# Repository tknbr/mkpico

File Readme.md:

# MKPico, a Pi pico USB Keyboard framework

Welcome to **MKPico**, a framework designed for creating custom keyboard firmware using the Raspberry Pi Pico microcontroller. MKPico is built using **FreeRTOS**, **Pico SDK** and **tinyUSB**.

<center>Selenium s (34 keys split mechanical keyboard)</center>

## Overview

This repository is the home of MKPico, and it includes everything you need to get started with developing your own keyboard firmware. MKPico abstracts the complexities of USB communication and real-time task management, providing an easy-to-use framework that is both powerful and efficient.

The first project built using MKPico is Selenium S, a custom 34-key split keyboard that demonstrates the capabilities of the framework. Selenium S serves as a reference implementation and a starting point for your own projects.

The main goals of the project are:

- **Cross-Platform Compatibility**: MKPico ensures that your keyboards work seamlessly across multiple operating systems, including Linux and Windows.
- **Support for Boot and Normal Modes**: The framework fully supports USB boot mode, making your keyboard operational even during system boot (BIOS/UEFI) and in the normal operating system environment.
Real-Time Operating System: Powered by FreeRTOS, MKPico offers real-time task management, allowing for precise control over keyboard functions and responsiveness.
- **USB Protocol Management**: Built on TinyUSB, MKPico handles USB communication reliably, ensuring your keyboard is fully compliant with USB standards.
- **Modular Design**: MKPico’s modular architecture allows you to extend or customize the framework to suit specific needs, whether it’s adding new HID features or integrating with other hardware components.
- **Easy porting to new keyboard designs**: The repository should allow to create new keyboard designs easily by defining a new layout and some key characteristics.

## Project Structure

The MKPico project is organized into several key directories, each serving a specific purpose in the development and configuration of custom keyboards. Below is an overview of the project structure:

- **`config/`**:
  - This folder contains configuration files for specific keyboards. Each keyboard has its own configuration file, which defines settings such as the key layout, pin mappings, and any special features or behaviors unique to that keyboard. By modifying these files, you can easily adapt MKPico to support different keyboard designs.

- **`include/`**:
  - The `include` directory houses the internal API headers that define the interfaces and data structures used throughout the MKPico framework. These headers are essential for maintaining a clear and consistent API across different modules of the project, making it easier to develop and extend functionality.

- **`src/`**:
  - This folder contains the core logic of the MKPico framework. It includes the following components:
    - **Internal I2C Communication**: Manages communication between the split halves of the keyboard, ensuring synchronized key presses and other functions across the two parts.
    - **USB Interface**: Handles the USB communication with the host computer, including enumeration, report generation, and processing of USB HID events.
    - **Logic of Layers and Key Map**: Implements the functionality for keyboard layers and key mapping, allowing users to define multiple layouts and switch between them dynamically.
    - **Keystrokes Handling**: Processes key presses and releases, manages debouncing, and ensures accurate and responsive input detection.

## Getting started

This section guides you through setting up the environment to work with FreeRTOS and the Raspberry Pi Pico SDK.

### 1. Clone FreeRTOS Repository

First, clone the FreeRTOS kernel repository:

```bash
git clone https://github.com/FreeRTOS/FreeRTOS-Kernel.git
cd FreeRTOS-Kernel
```

And move to the smp branch that supports multiple core:

```bash
git checkout -t remotes/origin/smp
git submodule update --init
```

### 2. Clone Pico SDK Repository

Second, clone the Pico SDK repository:

```bash
git clone https://github.com/raspberrypi/pico-sdk.git
cd pico-sdk
git submodule update --init
```

### 3. Set environment variables 

Set environment variables to point to the FreeRTOS and Pico SDK directories:

```bash
export FREERTOS_KERNEL_PATH=/path/to/FreeRTOS-Kernel
export PICO_SDK_PATH=/path/to/pico-sdk
```

### 4. Initialize project code

Now, clone your project repository and initialize it.

```bash
cd /path/to/your/workspace
git clone https://github.com/tknbr/mkpico.git
cd mkpico
git submodule update --init
```

### 5. Set up CMake and Build the Project

You can now set up CMake and build the project:

```bash
mkdir build
cd build
cmake ..
make
```

## Acknowledgements

The development of MKPico and the Selenium S keyboard was greatly influenced and supported by the vibrant communities dedicated to mechanical keyboards and custom firmware development. We would like to extend our gratitude to the following communities and content creators for their invaluable resources, tutorials, and inspiration:

- **Mechanical Keyboard Enthusiasts on GitHub**: The numerous open-source keyboard projects and libraries available on GitHub have been instrumental in shaping the direction of MKPico. Special thanks to repositories like [QMK Firmware](https://github.com/qmk/qmk_firmware), which provided insight into advanced keyboard features and firmware structure.
  
- **YouTube Content Creators**: Channels such as [Joe Scotto](https://www.youtube.com/@joe_scotto) and [Ben Vallack](https://www.youtube.com/c/BenVallack) have offered detailed build guides, reviews, and deep dives into keyboard design that have been incredibly helpful during the development process.

- **Online Keyboard Communities**: Platforms like [r/MechanicalKeyboards](https://www.reddit.com/r/MechanicalKeyboards/) on Reddit, and forums like [Geekhack](https://geekhack.org/), have provided a wealth of information and community support that was crucial in overcoming challenges during the project.

This project would not have been possible without the contributions of these communities, and we encourage anyone interested in custom keyboard development to explore these resources and get involved.

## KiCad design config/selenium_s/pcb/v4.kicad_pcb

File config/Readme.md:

## Configuration Folder Overview

The `config` folder is dedicated to holding all the configuration settings for the different parts of the project. This modular configuration structure allows for easy management and customization of various components of the firmware.

### 1. FreeRTOSConfig.h

**Purpose:**
- `FreeRTOSConfig.h` contains the configuration settings for the FreeRTOS kernel.
- It defines various parameters like task priorities, stack sizes, tick rates, and other kernel-level settings required by FreeRTOS to operate within the environment.

### 2. Compile.h

**Purpose:**
- `compile.h` contains two important defines: `PERIPHERAL` and `CONTROLLER`.
- These defines determine whether the compiled firmware image will be for the peripheral or the controller part of the keyboard.
- **Future Enhancement:** The goal is to eventually move this configuration to the Makefile so that users won't need to modify this file directly.

### 3. Task_Internal.h

**Purpose:**
- `task_internal.h` holds configuration details related to tasks within the firmware.
- This includes default sleep times, sizes of communication queues, default task priorities, and other task-specific settings that influence the behavior and performance of the system.

### 4. Tusb_Config.h

**Purpose:**
- `tusb_config.h` provides the basic configuration settings for the TinyUSB library.
- It includes settings related to USB device functionality, such as endpoint sizes, buffer sizes, and other parameters that TinyUSB requires to manage USB communication.

### 5. Keyboard-Specific Configurations

**Purpose:**
- The `config` folder also contains a subfolder for each keyboard supported by the firmware. Currently, there is one folder called `selenium_s`.
- Each keyboard-specific folder contains the following files:
  - **gpios.h:** Defines the GPIOs associated with each column and row of the keyboard matrix. This file maps the physical layout of the keyboard to the microcontroller's GPIO pins.
  - **keymap.h:** Provides the layout of the rows and columns, linking the physical keyboard matrix to the logical keymap.
  - **keymap.c:** Contains the definition of the keyboard's layout and the specific location of each key. This file is where the actual key mappings (e.g., which key corresponds to which row/column) are defined.
  - **pcb:** this folder contains the schematic and pcb files for the keyboard.

  <center>Selenium s (34 keys split mechanical keyboard) pcb</center>

### Summary

The `config` folder is the backbone of the project's configuration management, encapsulating all necessary settings to customize the FreeRTOS kernel, task behaviors, USB communication, and keyboard layouts. By modularizing these settings into distinct files and folders, the project ensures that configurations are easy to manage, modify, and extend, making the firmware highly adaptable to different hardware configurations and future enhancements.

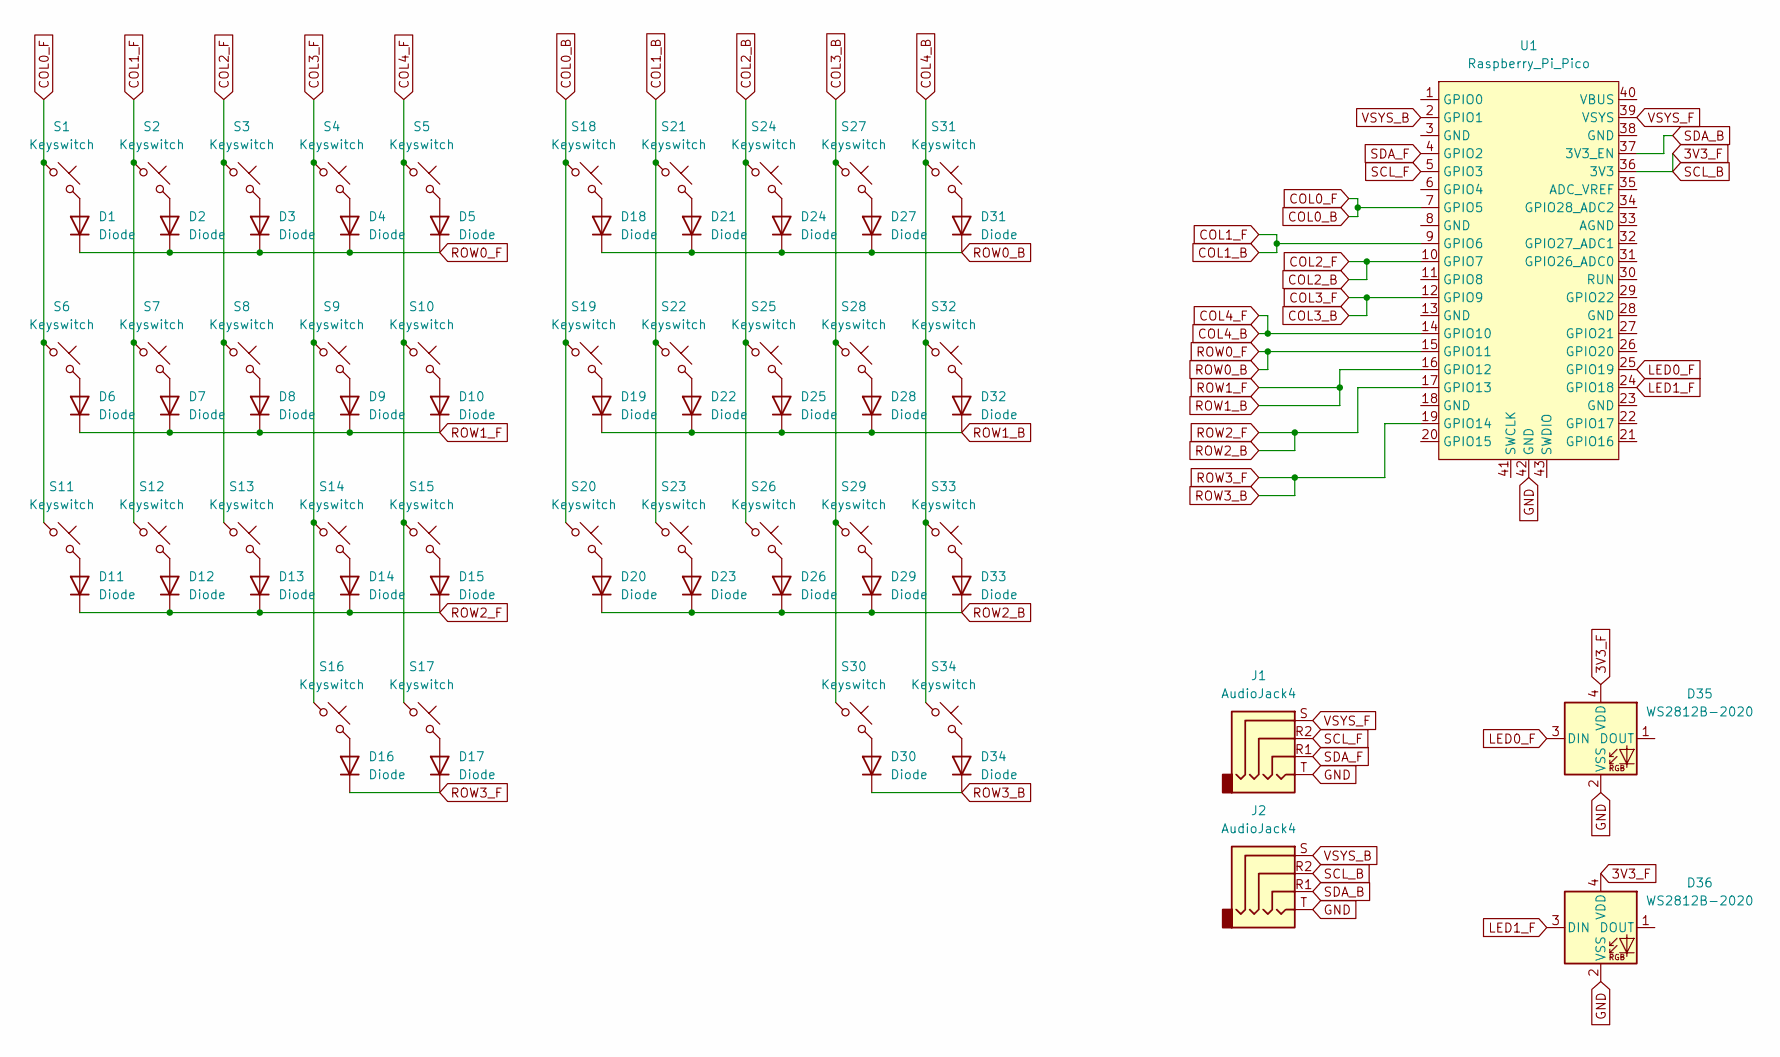
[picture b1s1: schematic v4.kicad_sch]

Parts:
D1, D2, D3, D4, D5, D6, D7, D8, D9, D10, D11, D12, D13, D14, D15, D16, D17, D18, D19, D20, D21, D22, D23, D24, D25, D26, D27, D28, D29, D30, D31, D32, D33, D34: Diode; Diode_SOD-123
D35, D36: WS2812B-2020; LED_WS2812B-2020_PLCC4_2.0x2.0mm
J1, J2: AudioJack4; Jack_3.5mm_PJ320D_Horizontal
S1, S2, S3, S4, S5, S6, S7, S8, S9, S10, S11, S12, S13, S14, S15, S16, S17, S18, S19, S20, S21, S22, S23, S24, S25, S26, S27, S28, S29, S30, S31, S32, S33, S34: Keyswitch; Hotswap_MX_1.00u
U1: Raspberry_Pi_Pico

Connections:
3V3_F: D35.4 (VDD), D36.4 (VDD), J2.R2, U1.36 (3V3)
COL0_B: S1.1, S6.1, S11.1, S18.1, S19.1, S20.1, U1.7 (GPIO5)
COL1_B: S2.1, S7.1, S12.1, S21.1, S22.1, S23.1, U1.9 (GPIO6)
COL2_B: S3.1, S8.1, S13.1, S24.1, S25.1, S26.1, U1.10 (GPIO7)
COL3_B: S4.1, S9.1, S14.1, S16.1, S27.1, S28.1, S29.1, S30.1, U1.12 (GPIO9)
COL4_B: S5.1, S10.1, S15.1, S17.1, S31.1, S32.1, S33.1, S34.1, U1.14 (GPIO10)
GND: D35.2 (VSS), D36.2 (VSS), J1.T, J2.T, U1.42 (GND)
LED0_F: D35.3 (DIN), U1.25 (GPIO19)
LED1_F: D36.3 (DIN), U1.24 (GPIO18)
unnamed: D1.2 (A), S1.2
unnamed: D2.2 (A), S2.2
unnamed: D3.2 (A), S3.2
unnamed: D4.2 (A), S4.2
unnamed: D5.2 (A), S5.2
unnamed: D6.2 (A), S6.2
unnamed: D7.2 (A), S7.2
unnamed: D8.2 (A), S8.2
unnamed: D9.2 (A), S9.2
unnamed: D10.2 (A), S10.2
unnamed: D11.2 (A), S11.2
unnamed: D12.2 (A), S12.2
unnamed: D13.2 (A), S13.2
unnamed: D14.2 (A), S14.2
unnamed: D15.2 (A), S15.2
unnamed: D16.2 (A), S16.2
unnamed: D17.2 (A), S17.2
unnamed: D18.2 (A), S18.2
unnamed: D19.2 (A), S19.2
unnamed: D20.2 (A), S20.2
unnamed: D21.2 (A), S21.2
unnamed: D22.2 (A), S22.2
unnamed: D23.2 (A), S23.2
unnamed: D24.2 (A), S24.2
unnamed: D25.2 (A), S25.2
unnamed: D26.2 (A), S26.2
unnamed: D27.2 (A), S27.2
unnamed: D28.2 (A), S28.2
unnamed: D29.2 (A), S29.2
unnamed: D30.2 (A), S30.2
unnamed: D31.2 (A), S31.2
unnamed: D32.2 (A), S32.2
unnamed: D33.2 (A), S33.2
unnamed: D34.2 (A), S34.2
ROW0_B: D1.1 (K), D2.1 (K), D3.1 (K), D4.1 (K), D5.1 (K), D18.1 (K), D21.1 (K), D24.1 (K), D27.1 (K), D31.1 (K), U1.15 (GPIO11)
ROW1_B: D6.1 (K), D7.1 (K), D8.1 (K), D9.1 (K), D10.1 (K), D19.1 (K), D22.1 (K), D25.1 (K), D28.1 (K), D32.1 (K), U1.16 (GPIO12)
ROW2_B: D11.1 (K), D12.1 (K), D13.1 (K), D14.1 (K), D15.1 (K), D20.1 (K), D23.1 (K), D26.1 (K), D29.1 (K), D33.1 (K), U1.17 (GPIO13)
ROW3_B: D16.1 (K), D17.1 (K), D30.1 (K), D34.1 (K), U1.19 (GPIO14)
SCL_F: J1.R2, U1.5 (GPIO3)
SDA_B: J2.R1, U1.37 (3V3_EN)
SDA_F: J1.R1, U1.4 (GPIO2)
VSYS_B: J2.S, U1.2 (GPIO1)
VSYS_F: J1.S, U1.39 (VSYS)

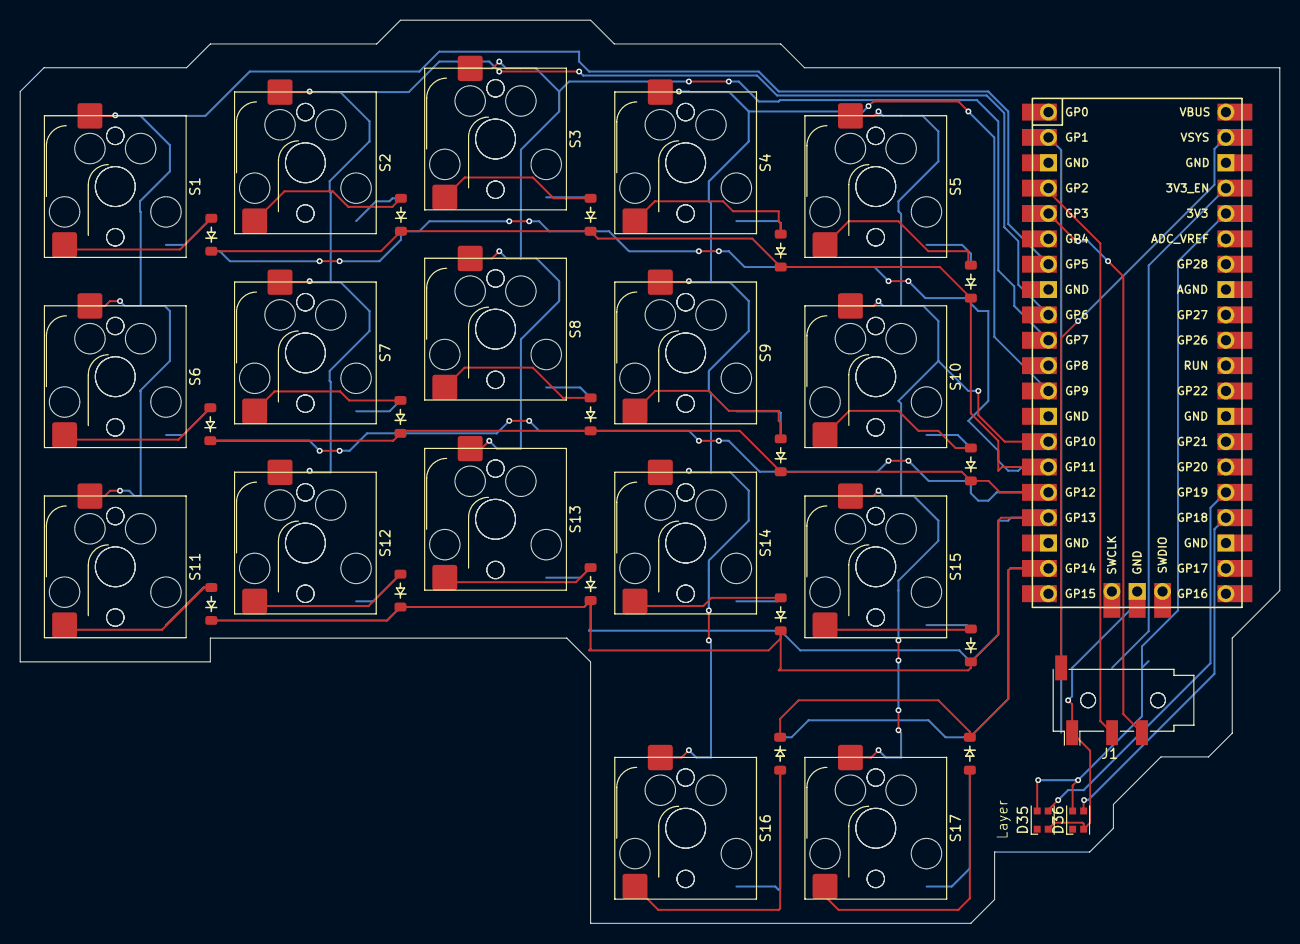
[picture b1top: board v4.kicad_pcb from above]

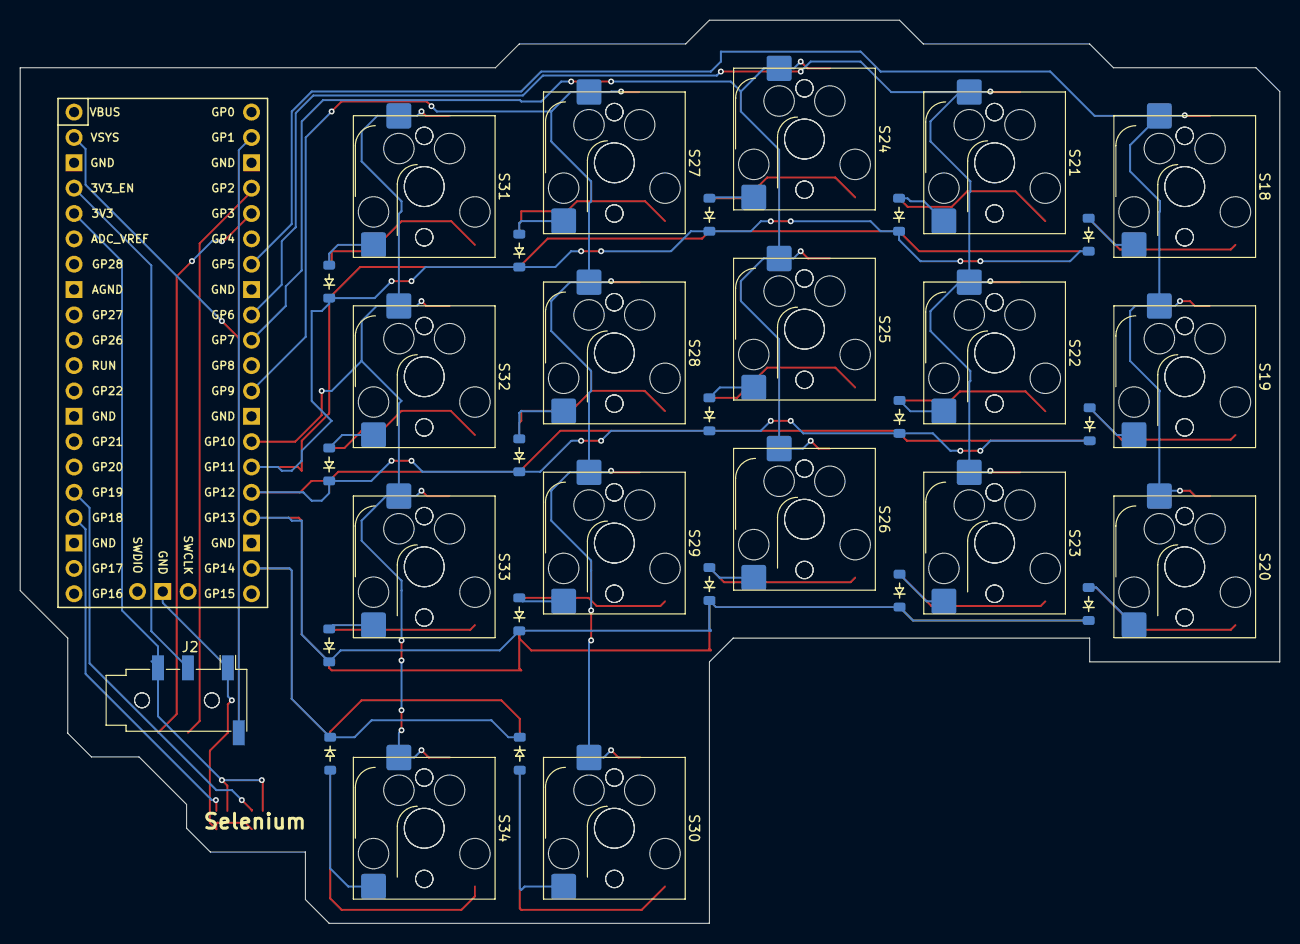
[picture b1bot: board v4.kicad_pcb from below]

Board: 2 copper layers, 126.2 x 90.5 mm, 73 parts (35 on the bottom side), 52 nets.

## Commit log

2024-06-29 mkpico structure and dummy files
2024-06-30 keystrokes.c first draft
2024-07-01 Added 10 ms delay once we put 1 in col
2024-07-01 queues between keystrokes and brain
2024-07-04 comm_internal skeleton
2024-07-06 debouncing
2024-07-08 Pico working as a usb keyboard device
2024-07-12 keymap with layer 0
2024-07-24 First layout working
2024-07-26 fix multiple keys resported at the same time
2024-07-26 decreased task wait
2024-08-09 removed useless vTaskDelay
2024-08-09 docu for usb descriptors
2024-08-10 replaced tabs with spaces
2024-08-10 Avoid multiple reports of same key + new layout
2024-08-10 modifiers reported correctly and led set when layer up
2024-08-11 main Readme
2024-08-11 acknowledgment update on readme
2024-08-11 include cleanup and ordering
2024-08-11 func definitions in .h files
2024-08-13 selenium s keymap updated
2024-08-16 Getting started section in main readme
2024-08-16 src readme added
2024-08-17 Readme added in config + cleanup of unused files
2024-08-17 Modifier keys only sent together with regular keys
2024-10-02 Added pcb & schematic files for seleium s
2024-10-02 fixed image path
2024-10-02 selenium s pcb image path fixed
